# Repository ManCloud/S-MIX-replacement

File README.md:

# S-MIX-replacement

Replacement PCB for broken SNES S-MIX ICs and N64 AMP-NUS ICs

## Contributors
 * borti4938
   * he had the original idea of this board and helped a lot with the redesign.

## Changelog

v20210526
 * Moved to KiCad
 * changed overall layout
 * optimized to use single-layer
 
## Nice-to-know

During my investigations I found out, that the S-MIX of the SNES and the AMP-NUS of the N64 are functional identical.
I even swapped the chips between consoles and everything worked like a charm.

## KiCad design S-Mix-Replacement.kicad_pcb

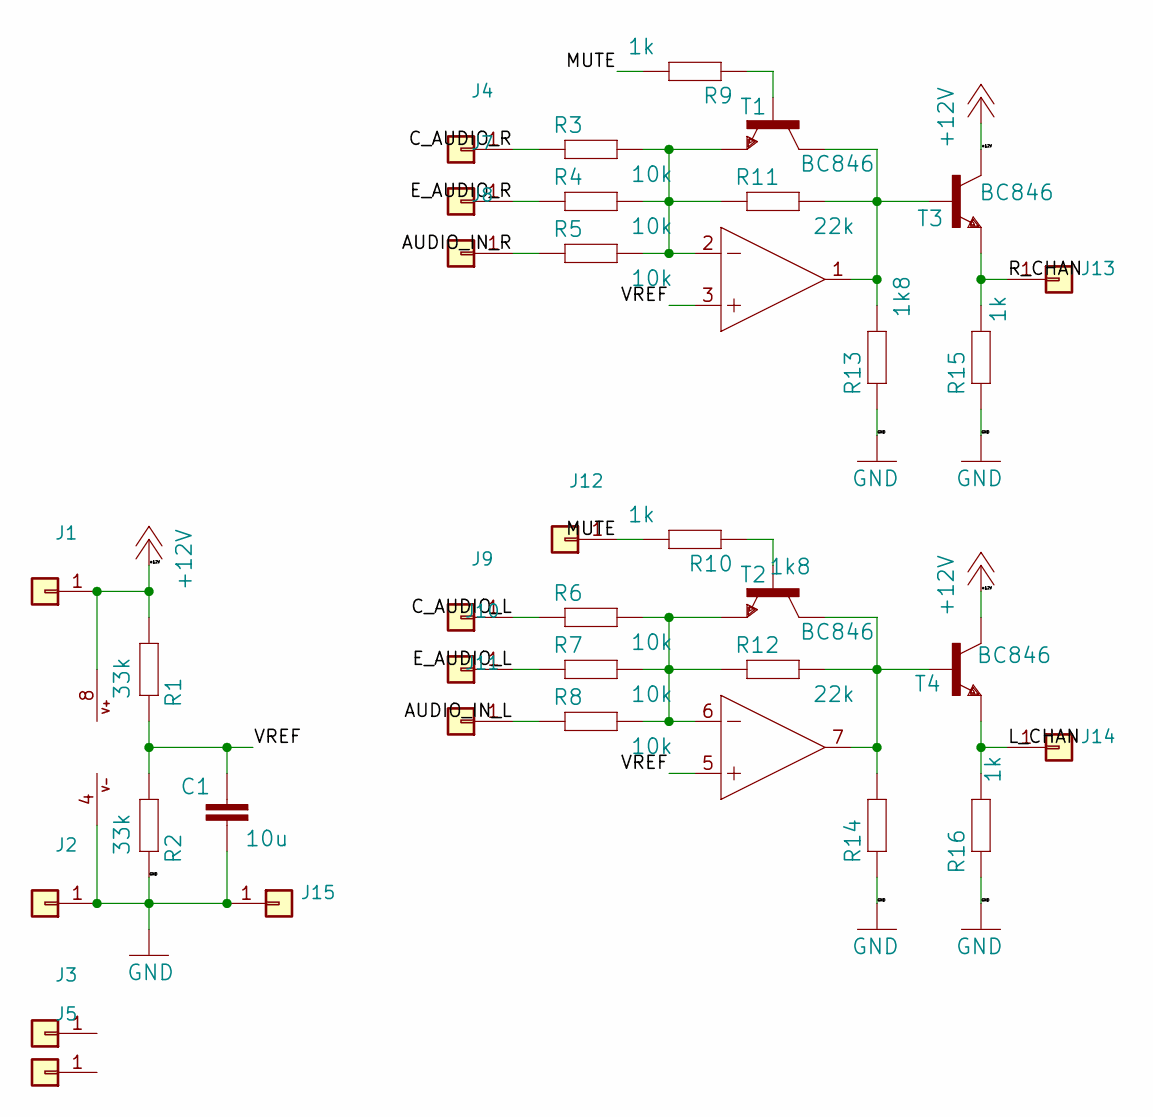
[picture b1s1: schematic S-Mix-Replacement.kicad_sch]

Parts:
C1: 10u; C_0805_2012Metric_Pad1.15x1.40mm_HandSolder
IC1: LM358D; SOIC-8_3.9x4.9mm_P1.27mm
J1, J2, J3, J4, J5, J7, J8, J9, J10, J11, J12, J13, J14, J15: TestPoint_THTPad_D1.0mm_Drill0.5mm
R1, R2: 33k; R_0603_1608Metric_Pad0.98x0.95mm_HandSolder
R3, R4, R5, R6, R7, R8: 10k; R_0603_1608Metric_Pad0.98x0.95mm_HandSolder
R9, R10, R15, R16: 1k; R_0603_1608Metric_Pad0.98x0.95mm_HandSolder
R11, R12: 22k; R_0603_1608Metric_Pad0.98x0.95mm_HandSolder
R13, R14: 1k8; R_0603_1608Metric_Pad0.98x0.95mm_HandSolder
T1, T2, T3, T4: BC846; SOT-23

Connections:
+12V: IC1.8 (V+), J1.1, R1.2, T3.3 (C), T4.3 (C)
/AUDIO_IN_L: J11.1, R8.1
/AUDIO_IN_R: J8.1, R5.1
/C_AUDIO_L: J9.1, R6.1
/C_AUDIO_R: J4.1, R3.1
/E_AUDIO_L: J10.1, R7.1
/E_AUDIO_R: J7.1, R4.1
/L_CHAN: J14.1, R16.2, T4.2 (E)
/MUTE: J12.1, R9.2, R10.2
/R_CHAN: J13.1, R15.2, T3.2 (E)
/VREF: C1.1, IC1.3 (+IN), IC1.5 (+IN), R1.1, R2.1
GND: C1.2, IC1.4 (V-), J2.1, J15.1, R2.2, R13.1, R14.1, R15.1, R16.1
unnamed: IC1.1 (OUT), R11.2, R13.2, T1.3 (C), T3.1 (B)
unnamed: IC1.2 (-IN), R3.2, R4.2, R5.2, R11.1, T1.2 (E)
unnamed: IC1.6 (-IN), R6.2, R7.2, R8.2, R12.1, T2.2 (E)
unnamed: IC1.7 (OUT), R12.2, R14.2, T2.3 (C), T4.1 (B)
unnamed: R9.1, T1.1 (B)
unnamed: R10.1, T2.1 (B)

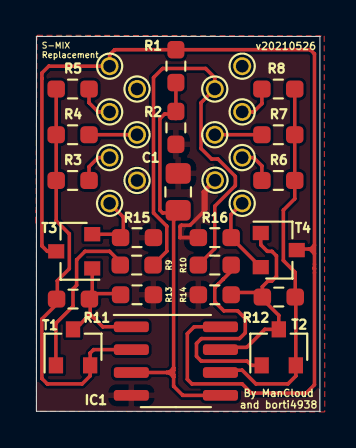
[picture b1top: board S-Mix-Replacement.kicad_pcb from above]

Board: 2 copper layers, 15.7 x 20.8 mm, 36 parts (0 on the bottom side), 18 nets.

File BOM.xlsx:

Qty | Value | Alternative | Package | Parts | Description
6 | 10k | - | R0805 | R3, R4, R5, R6, R7, R8 | RESISTOR, European symbol
1 | 10u | - | C1206 | C1 | CAPACITOR, European symbol
4 | 1k | - | R0805 | R9, R10, R15, R16 | RESISTOR, European symbol
2 | 1k8 | - | R0805 | R13, R14 | RESISTOR, European symbol
2 | 22k | 24k | R0805 | R11, R12 | RESISTOR, European symbol
2 | 33k | - | R0805 | R1, R2 | RESISTOR, European symbol
4 | BC846 | 2SC2412K | SOT23 | T1, T2, T3, T4 | NPN TRANSISTOR
1 | LM358D | - | SO08 | IC1 | OP AMP also LM158; LM258; LM2904

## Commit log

2022-01-02 Updated repo to v20210526
